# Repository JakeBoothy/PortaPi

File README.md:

# PortaPi
A portable Raspberry Pi Zero W2

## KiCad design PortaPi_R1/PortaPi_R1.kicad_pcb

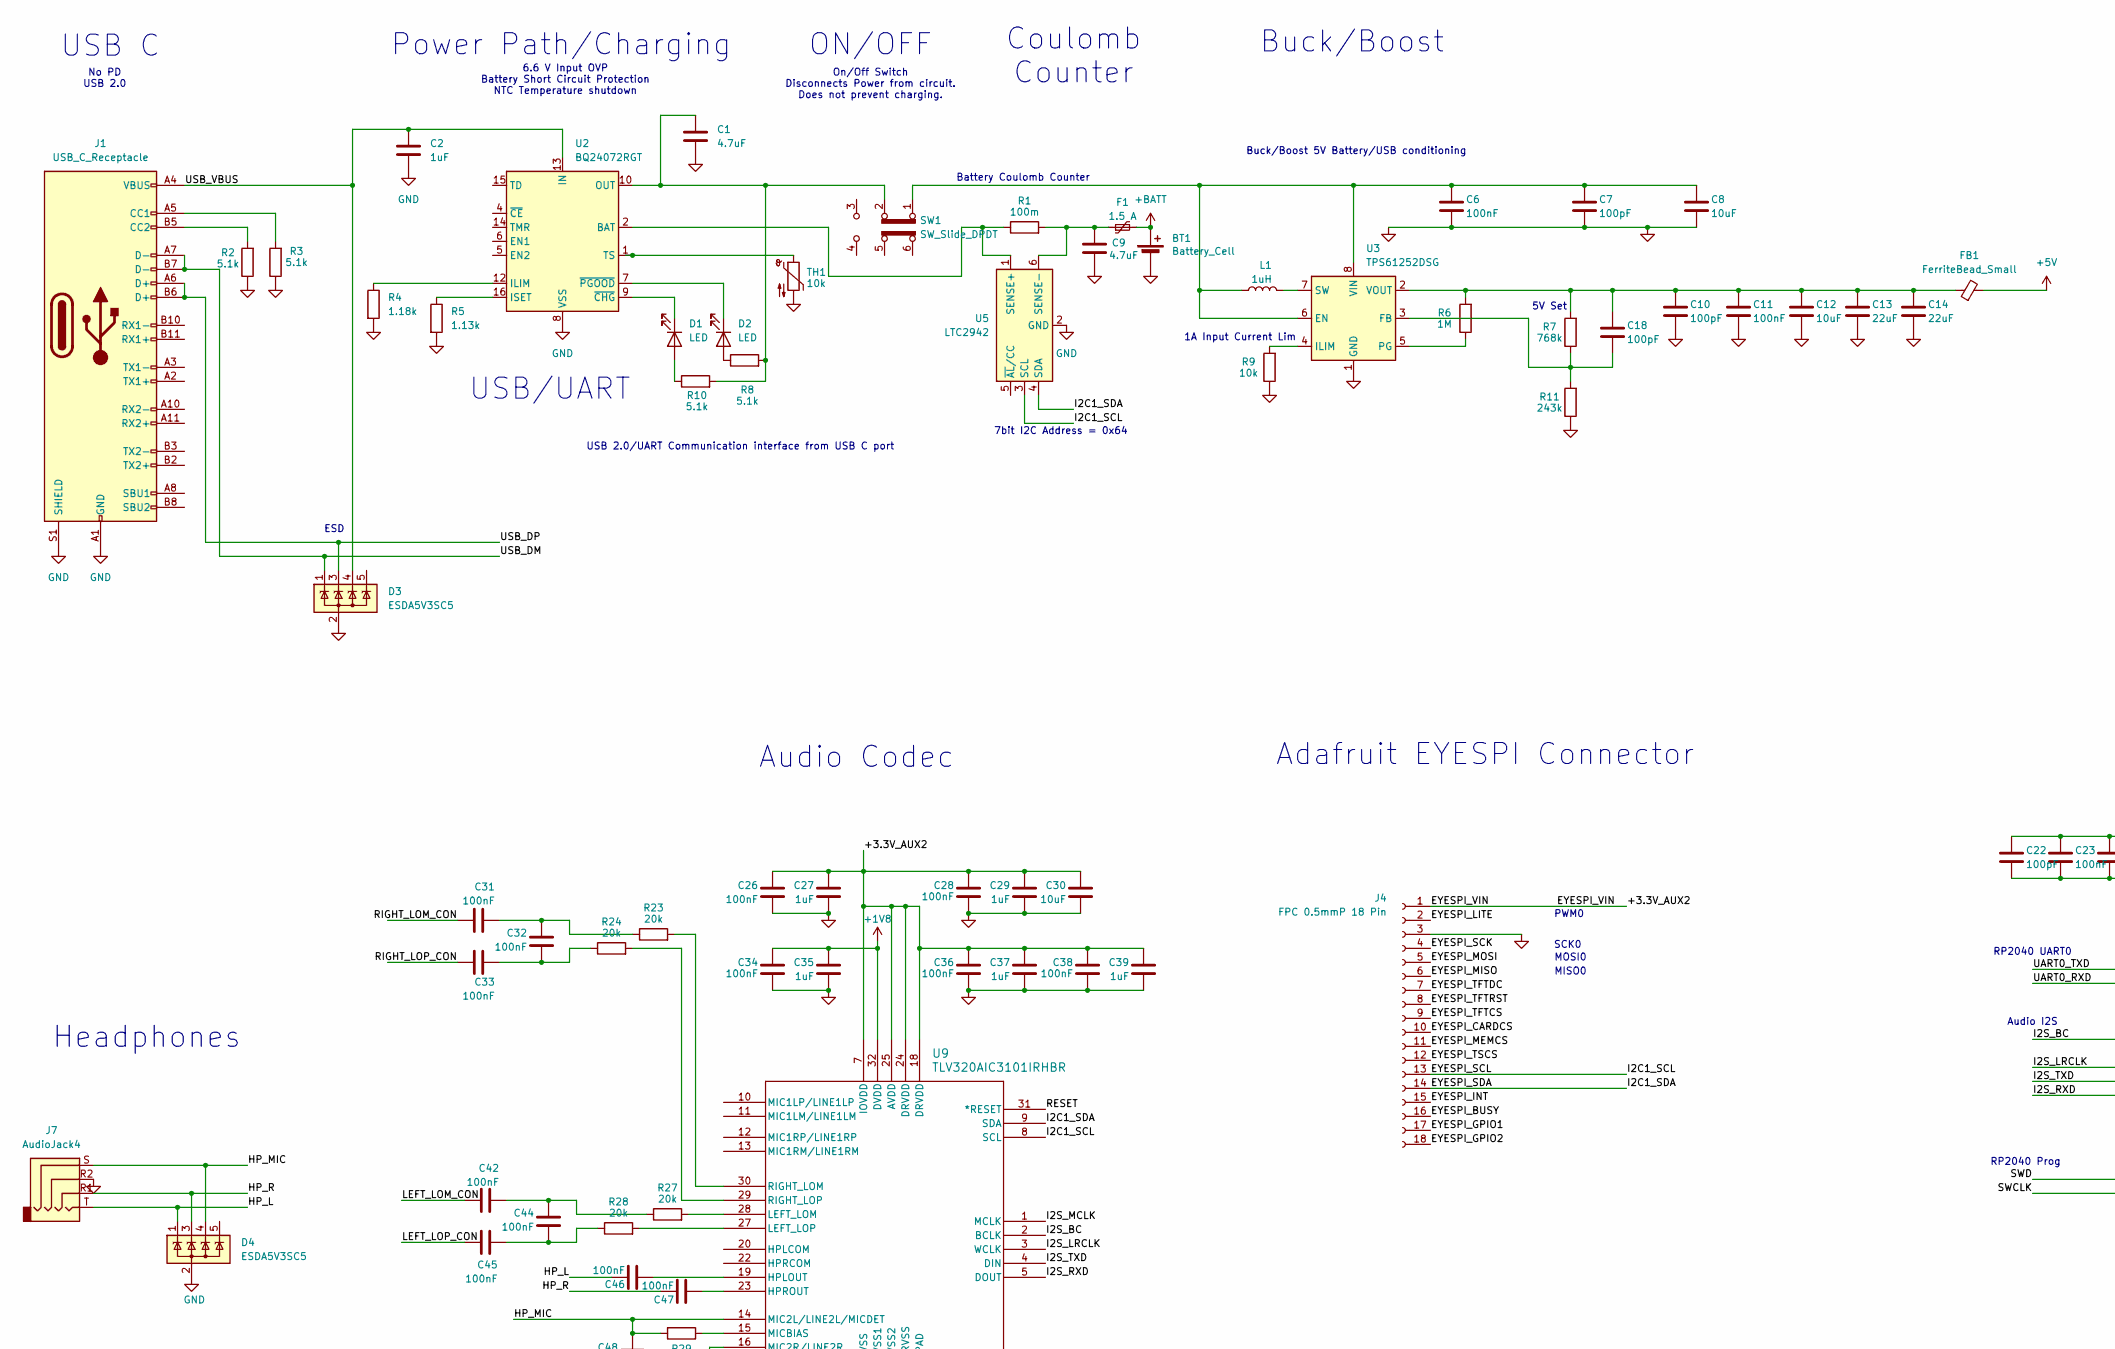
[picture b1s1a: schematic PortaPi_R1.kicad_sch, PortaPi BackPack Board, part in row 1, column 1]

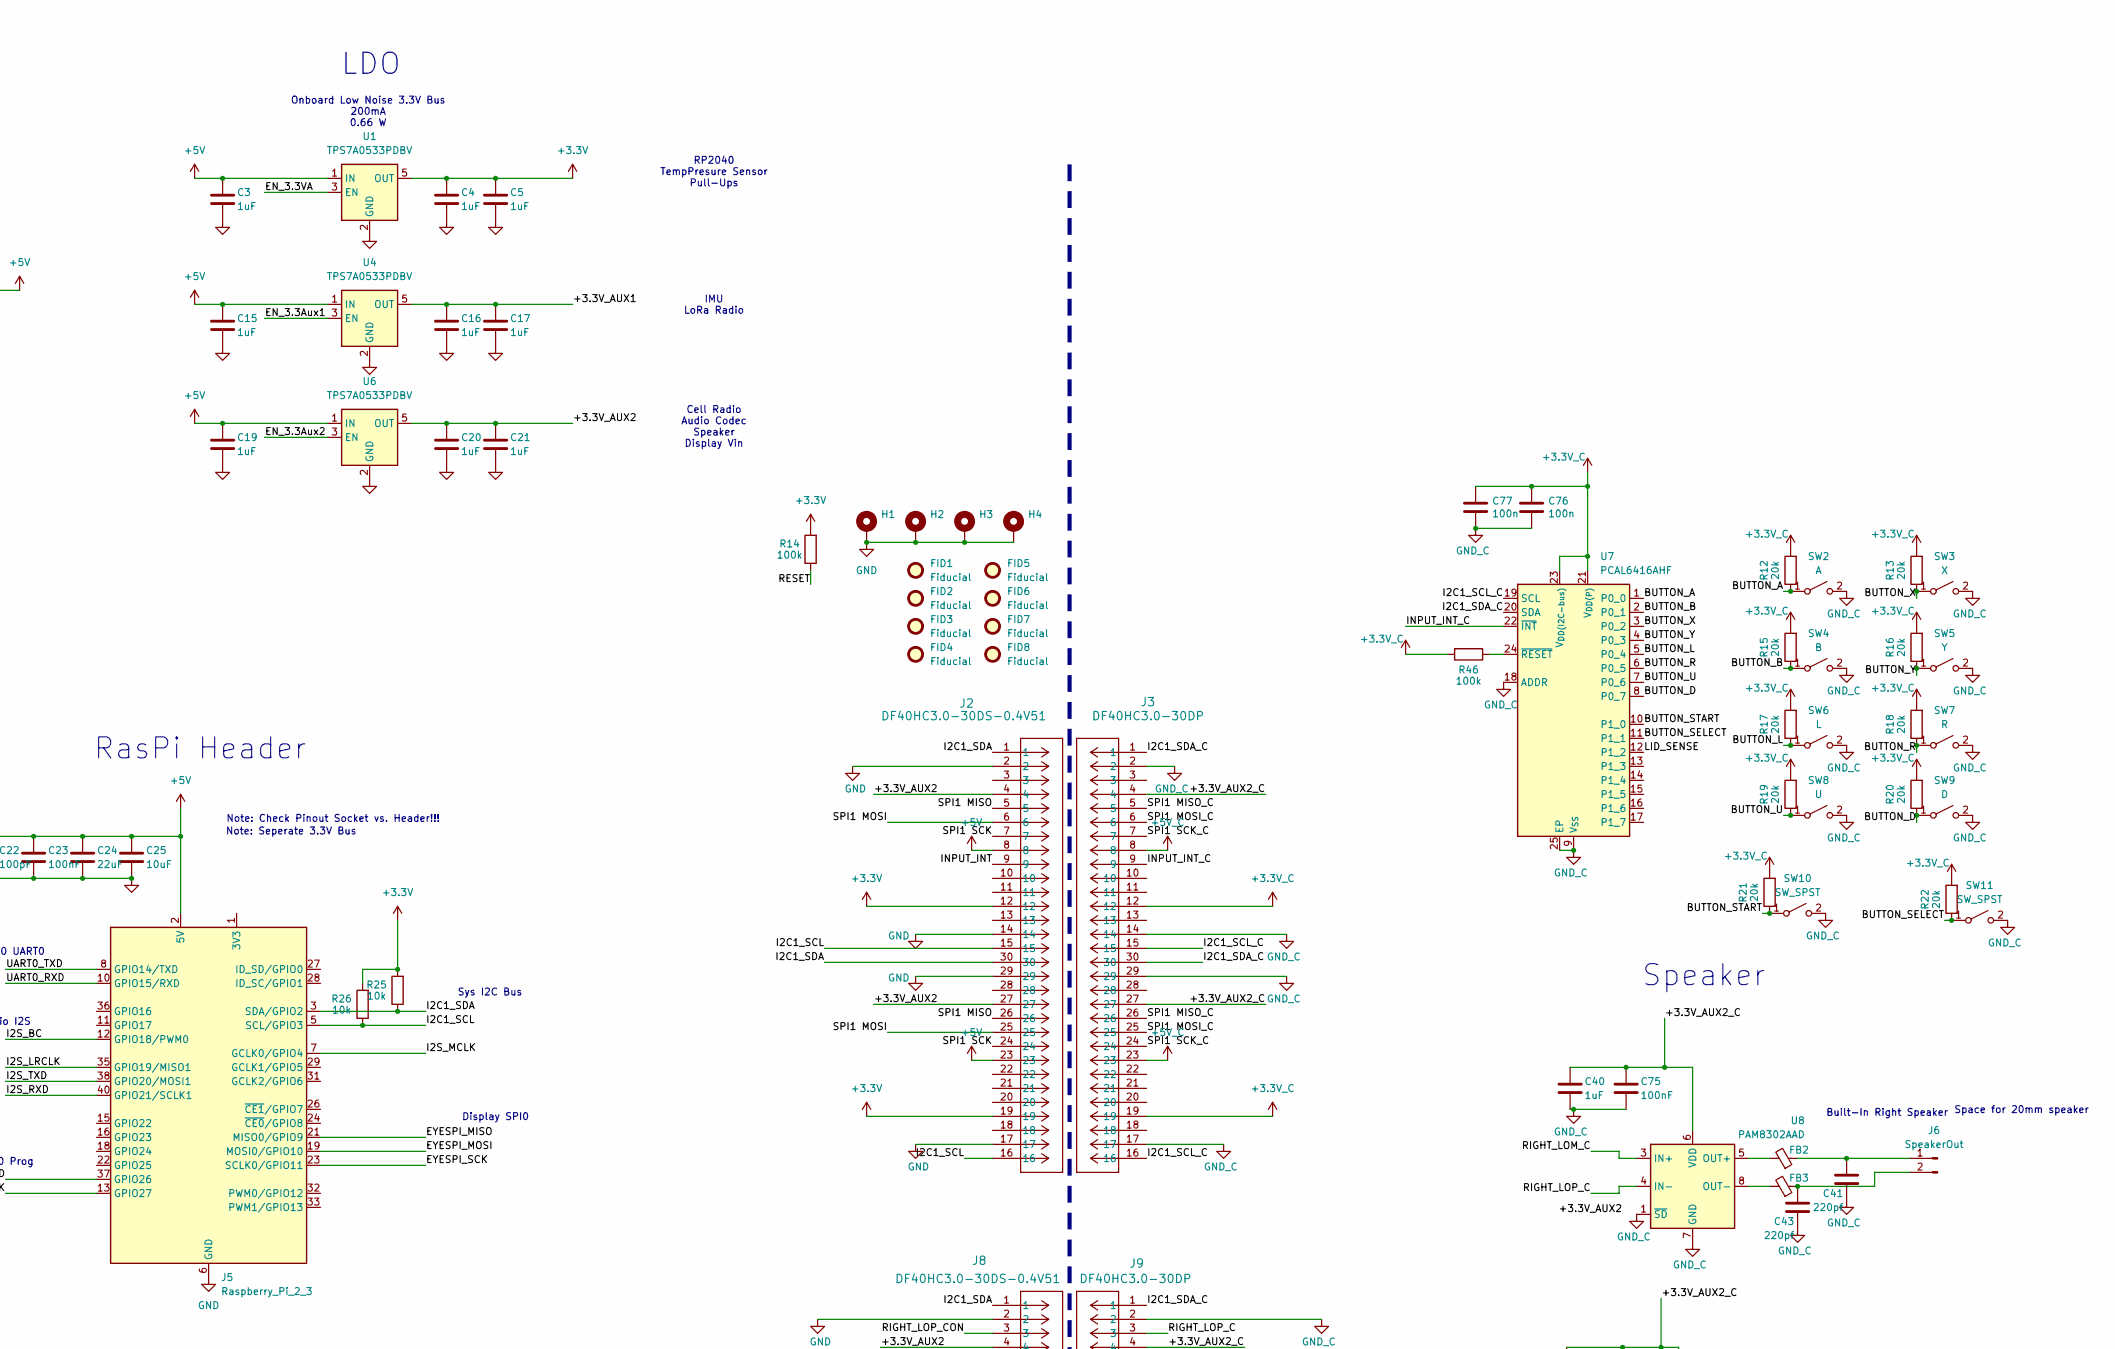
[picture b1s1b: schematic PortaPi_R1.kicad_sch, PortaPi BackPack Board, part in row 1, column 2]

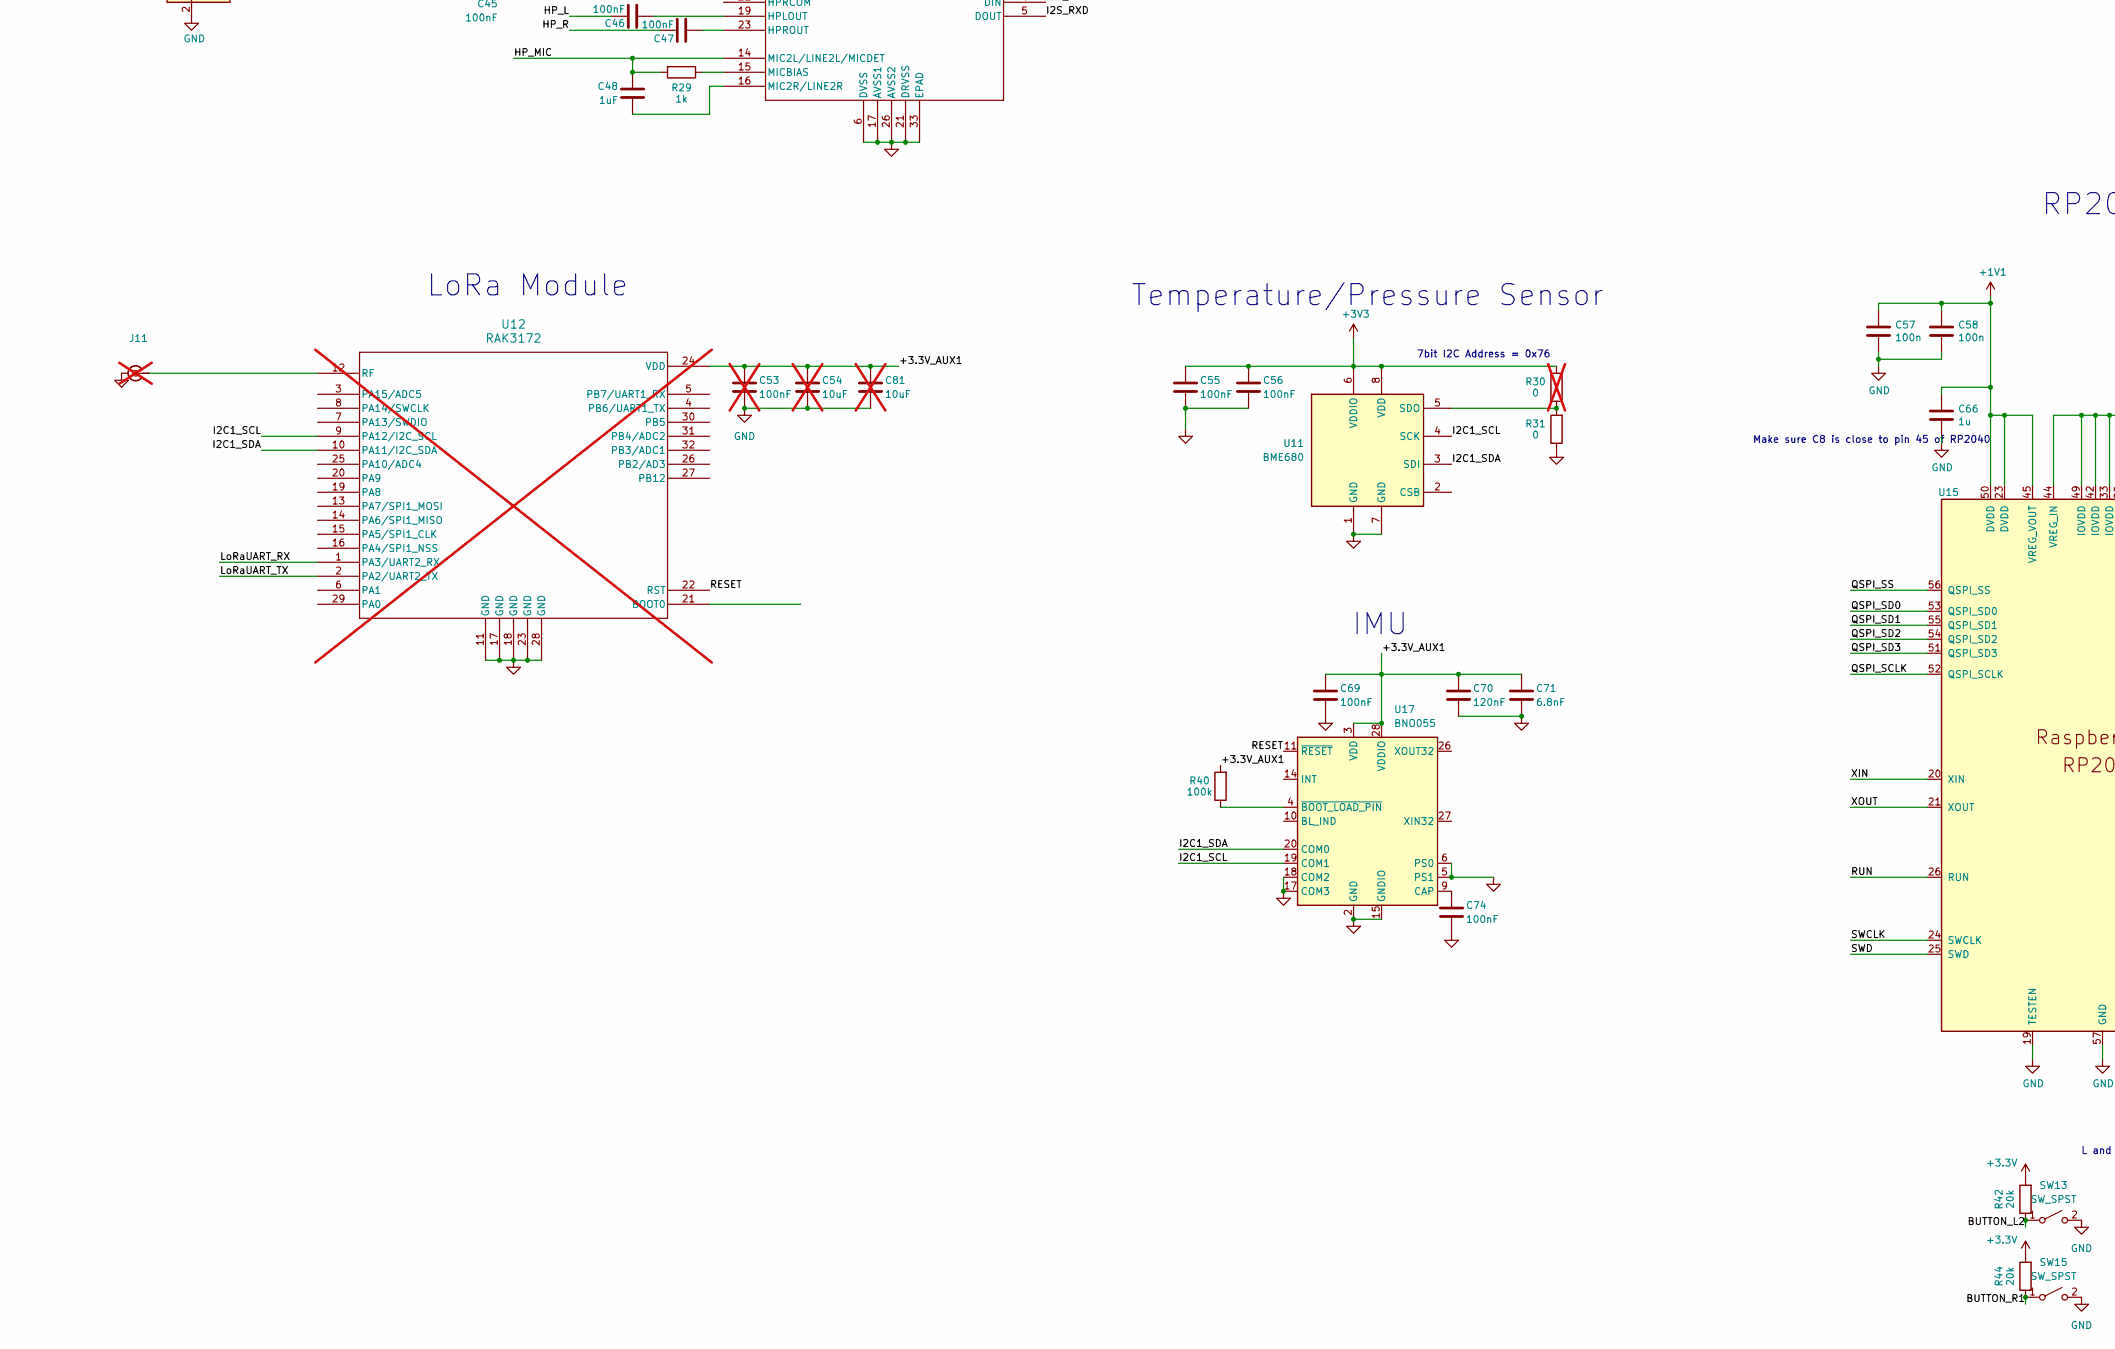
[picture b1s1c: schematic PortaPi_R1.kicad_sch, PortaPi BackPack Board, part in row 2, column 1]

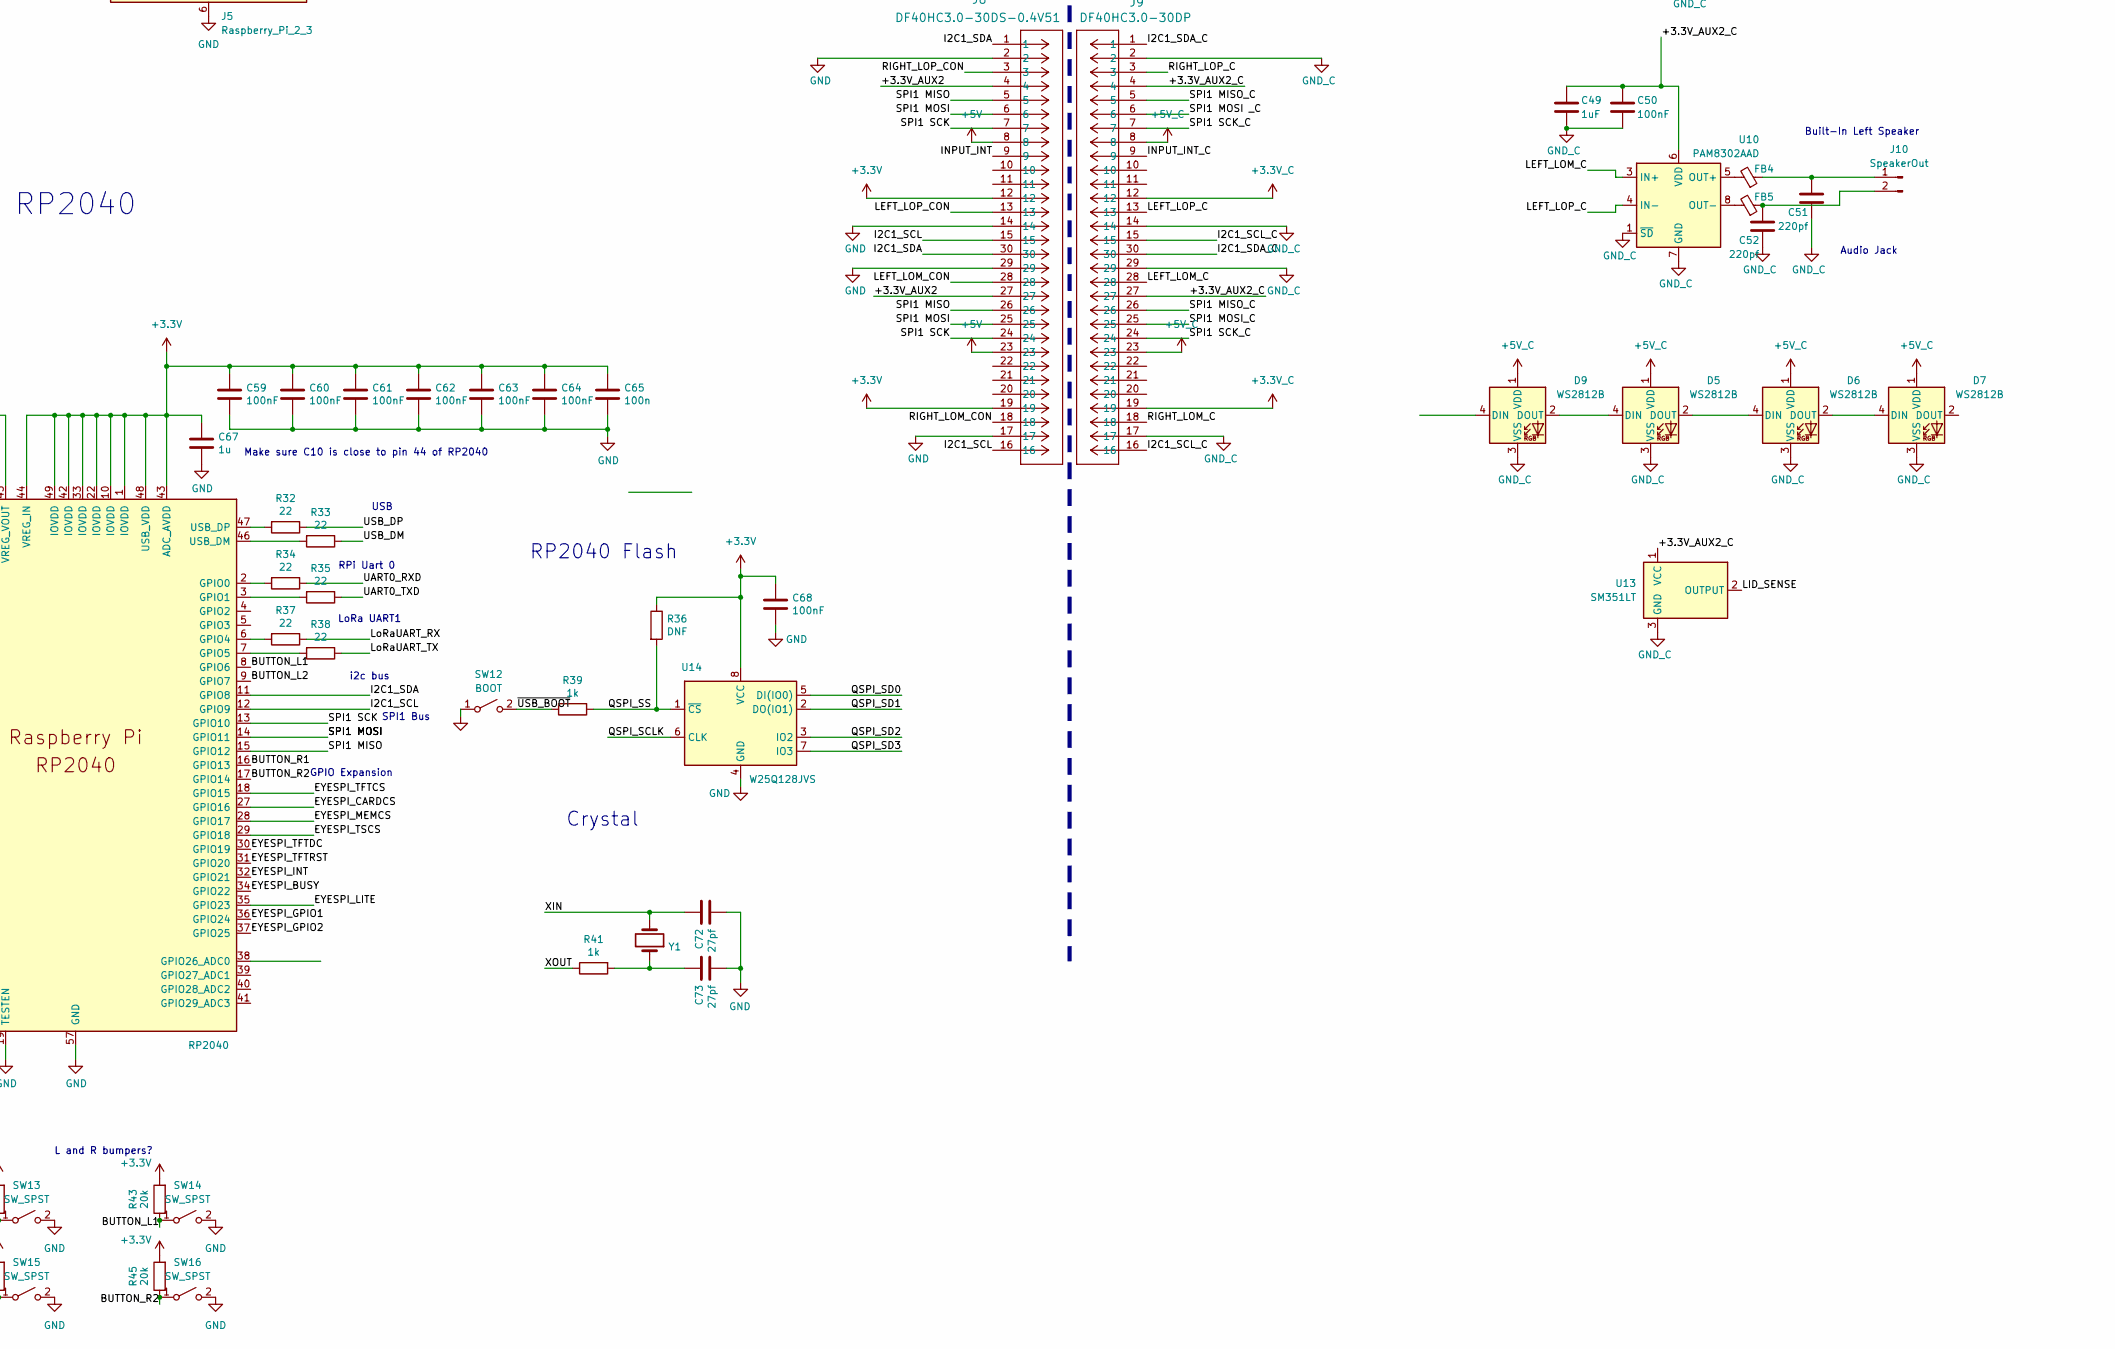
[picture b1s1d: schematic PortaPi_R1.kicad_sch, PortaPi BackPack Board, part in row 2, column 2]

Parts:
BT1: Battery_Cell; JST_PH_S2B-PH-SM4-TB_1x02-1MP_P2.00mm_Horizontal
C1, C9: 4.7uF; C_0805_2012Metric
C2, C3, C4, C5, C15, C16, C17, C19, C20, C21, C27, C29, C35, C37, C39, C40, C48, C49: 1uF; C_0603_1608Metric
C6, C11, C23, C26, C28, C31, C32, C33, C34, C36, C38, C42, C44, C45, C46, C47, C50, C55, C56, C68, C69, C74, C75: 100nF; C_0603_1608Metric
C7, C10, C18, C22: 100pF; C_0603_1608Metric
C8, C12, C25, C30: 10uF; C_0805_2012Metric
C13, C14, C24: 22uF; C_0805_2012Metric
C41, C43, C51, C52: 220pf; C_0603_1608Metric
C53: 100nF; C_0603_1608Metric; not fitted
C54, C81: 10uF; C_0805_2012Metric; not fitted
C57, C58, C65, C76, C77: 100n; C_0402_1005Metric
C59, C60, C61, C62, C63, C64: 100nF; C_0402_1005Metric
C66, C67: 1u; C_0402_1005Metric
C70: 120nF; C_0603_1608Metric
C71: 6.8nF; C_0603_1608Metric
C72, C73: 27pf; C_0402_1005Metric
D1, D2: LED; LED_0603_1608Metric
D3, D4: ESDA5V3SC5; SOT-23-5
D5, D6, D7, D9: WS2812B; LED_WS2812B_PLCC4_5.0x5.0mm_P3.2mm
F1: 1.5 A; R_0603_1608Metric
FB1: FerriteBead_Small; R_0603_1608Metric
FB2, FB3, FB4, FB5: FerriteBead_Small; L_0603_1608Metric
FID1, FID2, FID3, FID4, FID5, FID6, FID7, FID8: Fiducial; Fiducial_1.5mm_Mask3mm
H1, H2, H3, H4: MountingHole_Pad; MountingHole_2.5mm_Pad_Via
J1: USB_C_Receptacle; USB_C_Receptacle_GCT_USB4105-xx-A_16P_TopMnt_Horizontal
J2, J8: DF40HC3.0-30DS-0.4V51; CONN_30DS-0.4V51
J3, J9: DF40HC3.0-30DP; SOIC_0DP-0.4V51_HIR
J4: FPC 0.5mmP 18 Pin; TE_1-1734839-8_1x18-1MP_P0.5mm_Horizontal
J5: Raspberry_Pi_2_3; Raspberry_Pi_Zero_Socketed_THT_FaceDown_MountingHoles
J6, J10: SpeakerOut; SolderJumper-2_P1.3mm_Open_Pad1.0x1.5mm
J7: AudioJack4; Jack_3.5mm_PJ320D_Horizontal
J11: Conn_Coaxial_Small; U.FL_Molex_MCRF_73412-0110_Vertical; not fitted
L1: 1uH; L_Bourns-SRN4018
R1: 100m; R_0603_1608Metric
R2, R3, R8, R10: 5.1k; R_0603_1608Metric
R4: 1.18k; R_0603_1608Metric
R5: 1.13k; R_0603_1608Metric
R6: 1M; R_0603_1608Metric
R7: 768k; R_0603_1608Metric
R9, R25, R26: 10k; R_0603_1608Metric
R11: 243k; R_0603_1608Metric
R12, R13, R15, R16, R17, R18, R19, R20, R21, R22, R23, R24, R27, R28, R42, R43, R44, R45: 20k; R_0603_1608Metric
R14, R40, R46: 100k; R_0603_1608Metric
R29: 1k; C_0603_1608Metric
R30: 0; R_0603_1608Metric; not fitted
R31: 0; R_0603_1608Metric
R32, R33, R34, R35, R37, R38: 22; C_0402_1005Metric
R36: DNF; C_0402_1005Metric
R39, R41: 1k; C_0402_1005Metric
SW1: SW_Slide_DPDT; SW_SPDT_PCM12
SW2: A; SW_PUSH_6mm
SW3: X; SW_PUSH_6mm
SW4: B; SW_PUSH_6mm
SW5: Y; SW_PUSH_6mm
SW6: L; SW_PUSH_6mm
SW7: R; SW_PUSH_6mm
SW8: U; SW_PUSH_6mm
SW9: D; SW_PUSH_6mm
SW10, SW11: SW_SPST; SW_PUSH_6mm
SW12: BOOT; SW_SPST_B3U-1000P-B
SW13, SW14, SW15, SW16: SW_SPST; SW_Tactile_SPST_Angled_PTS645Vx31-2LFS
TH1: 10k; R_0603_1608Metric
U1, U4, U6: TPS7A0533PDBV; SOT-23-5
U2: BQ24072RGT; VQFN-16-1EP_3x3mm_P0.5mm_EP1.6x1.6mm
U3: TPS61252DSG; WSON-8-1EP_2x2mm_P0.5mm_EP0.9x1.6mm
U5: LTC2942; DFN-6-1EP_3x2mm_P0.5mm_EP1.65x1.35mm
U7: PCAL6416AHF; HVQFN-24-1EP_4x4mm_P0.5mm_EP2.1x2.1mm
U8, U10: PAM8302AAD; SOP-8_3.9x4.9mm_P1.27mm
U9: TLV320AIC3101IRHBR; RHB32_3P45X3P45
U11: BME680; Bosch_LGA-8_3x3mm_P0.8mm_ClockwisePinNumbering
U12: RAK3172; RAK3172_RAK; not fitted
U13: SM351LT; SOT-23
U14: W25Q128JVS; SOIC-8_5.23x5.23mm_P1.27mm
U15: RP2040; QFN-56-1EP_7x7mm_P0.4mm_EP3.2x3.2mm
U17: BNO055; LGA-28_5.2x3.8mm_P0.5mm
Y1: ABM3-12.000MHZ-D2Y-T; Crystal_SMD_5032-4Pin_5.0x3.2mm

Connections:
+1V1: C57.1, C58.1, C66.1, U15.23 (DVDD), U15.45 (VREG_VOUT), U15.50 (DVDD)
+1V8: C34.1, C35.1, U9.32 (DVDD)
+3.3V: C4.1, C5.1, C59.1, C60.1, C61.1, C62.1, C63.1, C64.1, C65.1, C67.1, C68.1, J2.12, J2.19, J8.12, J8.19, R14.2, R25.2, R26.2, R36.1, R42.2, R43.2, R44.2, R45.2, U1.5 (OUT), U14.8 (VCC), U15.1 (IOVDD), U15.10 (IOVDD), U15.22 (IOVDD), U15.33 (IOVDD), U15.42 (IOVDD), U15.43 (ADC_AVDD), U15.44 (VREG_IN), U15.48 (USB_VDD), U15.49 (IOVDD)
+3.3V_C: C76.1, C77.1, J3.12, J3.19, J9.12, J9.19, R12.2, R13.2, R15.2, R16.2, R17.2, R18.2, R19.2, R20.2, R21.2, R22.2, R46.2, U7.21 (V_{DD(P)}), U7.23 (V_{DD(I2C-bus)})
+3V3: C55.1, C56.1, R30.2, U11.6 (VDDIO), U11.8 (VDD)
+5V: C3.1, C15.1, C19.1, C22.1, C23.1, C24.1, C25.1, FB1.2, J2.8, J2.23, J5.2 (5V), J5.4 (5V), J8.8, J8.23, U1.1 (IN), U4.1 (IN), U6.1 (IN)
+5V_C: D5.1 (VDD), D6.1 (VDD), D7.1 (VDD), D9.1 (VDD), J3.8, J3.23, J9.8, J9.23
+BATT: BT1.1 (+), F1.2
/+3.3V_AUX1: C16.1, C17.1, C53.1, C54.1, C69.1, C70.1, C71.1, C81.1, R40.2, U4.5 (OUT), U12.24 (VDD), U17.3 (VDD), U17.28 (VDDIO)
/+3.3V_AUX2: C20.1, C21.1, C26.1, C27.1, C28.1, C29.1, C30.1, C36.1, C37.1, C38.1, C39.1, J2.4, J2.27, J4.1, J8.4, J8.27, U6.5 (OUT), U9.7 (IOVDD), U9.18 (DRVDD), U9.24 (DRVDD), U9.25 (AVDD)
/+3.3V_AUX2_C: C40.1, C49.1, C50.1, C75.1, J3.4, J3.27, J9.4, J9.27, U8.6 (VDD), U10.6 (VDD), U13.1 (VCC)
/BUTTON_A: R12.1, SW2.1 (A), U7.1 (P0_0)
/BUTTON_B: R15.1, SW4.1 (A), U7.2 (P0_1)
/BUTTON_D: R20.1, SW9.1 (A), U7.8 (P0_7)
/BUTTON_L: R17.1, SW6.1 (A), U7.5 (P0_4)
/BUTTON_L1: R43.1, SW14.1 (A), U15.8 (GPIO6)
/BUTTON_L2: R42.1, SW13.1 (A), U15.9 (GPIO7)
/BUTTON_R: R18.1, SW7.1 (A), U7.6 (P0_5)
/BUTTON_R1: R44.1, SW15.1 (A), U15.16 (GPIO13)
/BUTTON_R2: R45.1, SW16.1 (A), U15.17 (GPIO14)
/BUTTON_SELECT: R22.1, SW11.1 (A), U7.11 (P1_1)
/BUTTON_START: R21.1, SW10.1 (A), U7.10 (P1_0)
/BUTTON_U: R19.1, SW8.1 (A), U7.7 (P0_6)
/BUTTON_X: R13.1, SW3.1 (A), U7.3 (P0_2)
/BUTTON_Y: R16.1, SW5.1 (A), U7.4 (P0_3)
/EN_3.3Aux1: U4.3 (EN)
/EN_3.3Aux2: U6.3 (EN)
/EN_3.3VA: U1.3 (EN)
/EYESPI_BUSY: J4.16, U15.34 (GPIO22)
/EYESPI_CARDCS: J4.10, U15.27 (GPIO16)
/EYESPI_GPIO1: J4.17, U15.36 (GPIO24)
/EYESPI_GPIO2: J4.18, U15.37 (GPIO25)
/EYESPI_INT: J4.15, U15.32 (GPIO21)
/EYESPI_LITE: J4.2, U15.35 (GPIO23)
/EYESPI_MEMCS: J4.11, U15.28 (GPIO17)
/EYESPI_MISO: J4.6, J5.21 (MISO0/GPIO9)
/EYESPI_MOSI: J4.5, J5.19 (MOSI0/GPIO10)
/EYESPI_SCK: J4.4, J5.23 (SCLK0/GPIO11)
/EYESPI_SCL: J2.15, J2.16, J4.13, J5.5 (SCL/GPIO3), J8.15, J8.16, R26.1, U5.3 (SCL), U9.8 (SCL), U11.4 (SCK), U12.9 (PA12/I2C_SCL), U15.12 (GPIO9), U17.19 (COM1)
/EYESPI_SDA: J2.1, J2.30, J4.14, J5.3 (SDA/GPIO2), J8.1, J8.30, R25.1, U5.4 (SDA), U9.9 (SDA), U11.3 (SDI), U12.10 (PA11/I2C_SDA), U15.11 (GPIO8), U17.20 (COM0)
/EYESPI_TFTCS: J4.9, U15.18 (GPIO15)
/EYESPI_TFTDC: J4.7, U15.30 (GPIO19)
/EYESPI_TFTRST: J4.8, U15.31 (GPIO20)
/EYESPI_TSCS: J4.12, U15.29 (GPIO18)
/HP_L: C46.1, D4.1 (K), J7.T
/HP_MIC: C48.1, D4.4 (K), J7.S, R29.2, U9.14 (MIC2L/LINE2L/MICDET)
/HP_R: C47.1, D4.3 (K), J7.R1
/I2C1_SCL_C: J3.15, J3.16, J9.15, J9.16, U7.19 (SCL)
/I2C1_SDA_C: J3.1, J3.30, J9.1, J9.30, U7.20 (SDA)
/I2S_BC: J5.12 (GPIO18/PWM0), U9.2 (BCLK)
/I2S_LRCLK: J5.35 (GPIO19/MISO1), U9.3 (WCLK)
/I2S_MCLK: J5.7 (GCLK0/GPIO4), U9.1 (MCLK)
/I2S_RXD: J5.40 (GPIO21/SCLK1), U9.5 (DOUT)
/I2S_TXD: J5.38 (GPIO20/MOSI1), U9.4 (DIN)
/INPUT_INT: J2.9, J8.9
/INPUT_INT_C: J3.9, J9.9, U7.22 (~INT)
/LEFT_LOM_C: J9.28, U10.3 (IN+)
/LEFT_LOM_CON: C42.1, J8.28
/LEFT_LOP_C: J9.13, U10.4 (IN-)
/LEFT_LOP_CON: C45.1, J8.13
/LID_SENSE: U7.12 (P1_2), U13.2 (OUTPUT)
/LoRaUART_RX: R37.1, U12.1 (PA3/UART2_RX)
/LoRaUART_TX: R38.1, U12.2 (PA2/UART2_TX)
/QSPI_SCLK: U14.6 (CLK), U15.52 (QSPI_SCLK)
/QSPI_SD0: U14.5 (DI(IO0)), U15.53 (QSPI_SD0)
/QSPI_SD1: U14.2 (DO(IO1)), U15.55 (QSPI_SD1)
/QSPI_SD2: U14.3 (IO2), U15.54 (QSPI_SD2)
/QSPI_SD3: U14.7 (IO3), U15.51 (QSPI_SD3)
/QSPI_SS: R36.2, R39.1, U14.1 (~CS), U15.56 (QSPI_SS)
/RESET: R14.1, U9.31 (*RESET), U12.22 (RST), U17.11 (~RESET)
/RIGHT_LOM_C: J9.18, U8.3 (IN+)
/RIGHT_LOM_CON: C31.1, J8.18
/RIGHT_LOP_C: J9.3, U8.4 (IN-)
/RIGHT_LOP_CON: C33.1, J8.3
/RUN: U15.26 (RUN)
/SPI1 MISO: J2.5, J2.26, J8.5, J8.26, U15.15 (GPIO12)
/SPI1 MISO_C: J3.5, J3.26, J9.5, J9.26
/SPI1 MOSI: J2.6, J2.25, J8.6, J8.25, U15.14 (GPIO11)
/SPI1 MOSI _C: J9.6
/SPI1 MOSI_C: J3.6, J3.25, J9.25
/SPI1 SCK: J2.7, J2.24, J8.7, J8.24, U15.13 (GPIO10)
/SPI1 SCK_C: J3.7, J3.24, J9.7, J9.24
/SWCLK: J5.13 (GPIO27), U15.24 (SWCLK)
/SWD: J5.37 (GPIO26), U15.25 (SWD)
/UART0_RXD: J5.10 (GPIO15/RXD), R34.1
/UART0_TXD: J5.8 (GPIO14/TXD), R35.1
/USB_DM: D3.1 (K), J1.A7 (D-), J1.B7 (D-), R33.1
/USB_DP: D3.3 (K), J1.A6 (D+), J1.B6 (D+), R32.1
/USB_VBUS: C2.1, D3.4 (K), J1.A4 (VBUS), J1.A9 (VBUS), J1.B4 (VBUS), J1.B9 (VBUS), U2.13 (IN)
/XIN: C72.1, U15.20 (XIN), Y1.2
/XOUT: R41.1, U15.21 (XOUT)
/~USB_BOOT: R39.2, SW12.2 (B)
GND: BT1.2 (-), C1.2, C2.2, C3.2, C4.2, C5.2, C6.2, C7.2, C8.2, C9.2, C10.2, C11.2, C12.2, C13.2, C14.2, C15.2, C16.2, C17.2, C19.2, C20.2, C21.2, C22.2, C23.2, C24.2, C25.2, C26.2, C27.2, C28.2, C29.2, C30.2, C34.2, C35.2, C36.2, C37.2, C38.2, C39.2, C53.2, C54.2, C55.2, C56.2, C57.2, C58.2, C59.2, C60.2, C61.2, C62.2, C63.2, C64.2, C65.2, C66.2, C67.2, C68.2, C69.2, C70.2, C71.2, C72.2, C73.2, C74.2, C81.2, D3.2 (A), D4.2 (A), H1.1, H2.1, H3.1, H4.1, J1.A1 (GND), J1.A12 (GND), J1.B1 (GND), J1.B12 (GND), J1.S1 (SHIELD), J2.2, J2.14, J2.17, J2.29, J4.3, J5.6 (GND), J5.9 (GND), J5.14 (GND), J5.20 (GND), J5.25 (GND), J5.30 (GND), J5.34 (GND), J5.39 (GND), J7.R2, J8.2, J8.14, J8.17, J8.29, J11.2 (Ext), R2.1, R3.1, R4.2, R5.2, R9.1, R11.1, R31.1, SW12.1 (A), SW13.2 (B), SW14.2 (B), SW15.2 (B), SW16.2 (B), TH1.2, U1.2 (GND), U2.8 (VSS), U2.17 (VSS), U3.1 (GND), U3.9 (GND), U4.2 (GND), U5.2 (GND), U6.2 (GND), U9.6 (DVSS), U9.17 (AVSS1), U9.21 (DRVSS), U9.26 (AVSS2), U9.33 (EPAD), U11.1 (GND), U11.7 (GND), U12.11 (GND), U12.17 (GND), U12.18 (GND), U12.23 (GND), U12.28 (GND), U14.4 (GND), U15.19 (TESTEN), U15.57 (GND), U17.2 (GND), U17.5 (PS1), U17.6 (PS0), U17.15 (GNDIO), U17.16 (GNDIO), U17.17 (COM3), U17.18 (COM2), U17.25 (GNDIO)
GND_C: C40.2, C41.1, C43.1, C49.2, C50.2, C51.1, C52.1, C75.2, C76.2, C77.2, D5.3 (VSS), D6.3 (VSS), D7.3 (VSS), D9.3 (VSS), J3.2, J3.14, J3.17, J3.29, J9.2, J9.14, J9.17, J9.29, SW2.2 (B), SW3.2 (B), SW4.2 (B), SW5.2 (B), SW6.2 (B), SW7.2 (B), SW8.2 (B), SW9.2 (B), SW10.2 (B), SW11.2 (B), U7.9 (V_{SS}), U7.18 (ADDR), U7.25 (EP), U8.1 (~SD), U8.7 (GND), U10.1 (~SD), U10.7 (GND), U13.3 (GND)
unnamed: C1.1, R8.2, R10.2, SW1.2 (B), U2.10 (OUT), U2.11 (OUT)
unnamed: C31.2, C32.1, R23.1
unnamed: C32.2, C33.2, R24.1
unnamed: C42.2, C44.1, R27.1
unnamed: C44.2, C45.2, R28.1
unnamed: C73.1, R41.2, Y1.1
unnamed: D1.2 (A), R10.1
unnamed: D1.1 (K), U2.9 (~CHG)
unnamed: D2.2 (A), R8.1
unnamed: D2.1 (K), U2.7 (~PGOOD)
unnamed: D5.4 (DIN), D9.2 (DOUT)
unnamed: D5.2 (DOUT), D6.4 (DIN)
unnamed: D6.2 (DOUT), D7.4 (DIN)
unnamed: J1.A5 (CC1), R3.2
unnamed: J1.B5 (CC2), R2.2
unnamed: J5.1 (3V3), J5.17 (3V3)
unnamed: C41.2, FB2.1, J6.1
unnamed: C43.2, FB3.1, J6.2
unnamed: C51.2, FB4.1, J10.1
unnamed: C52.2, FB5.1, J10.2
unnamed: J11.1 (In), U12.12 (RF)
unnamed: R4.1, U2.12 (ILIM)
unnamed: R5.1, U2.16 (ISET)
unnamed: TH1.1, U2.1 (TS)
unnamed: C6.1, C7.1, C8.1, L1.1, SW1.1 (A), U3.6 (EN), U3.8 (VIN)
unnamed: C18.2, R7.1, R11.2, U3.3 (FB)
unnamed: R9.2, U3.4 (ILIM)
unnamed: R6.1, U3.5 (PG)
unnamed: L1.2, U3.7 (SW)
unnamed: C10.1, C11.1, C12.1, C13.1, C14.1, C18.1, FB1.1, R6.2, R7.2, U3.2 (VOUT)
unnamed: R1.1, U2.2 (BAT), U2.3 (BAT), U5.1 (SENSE+)
unnamed: C9.1, F1.1, R1.2, U5.6 (SENSE-)
unnamed: R46.1, U7.24 (~RESET)
unnamed: FB2.2, U8.5 (OUT+)
unnamed: FB3.2, U8.8 (OUT-)
unnamed: C46.2, U9.19 (HPLOUT)
unnamed: C47.2, U9.23 (HPROUT)
unnamed: R27.2, U9.28 (LEFT_LOM)
unnamed: R28.2, U9.27 (LEFT_LOP)
unnamed: C48.2, U9.16 (MIC2R/LINE2R)
unnamed: R29.1, U9.15 (MICBIAS)
unnamed: R23.2, U9.30 (RIGHT_LOM)
unnamed: R24.2, U9.29 (RIGHT_LOP)
unnamed: FB4.2, U10.5 (OUT+)
unnamed: FB5.2, U10.8 (OUT-)
unnamed: R30.1, R31.2, U11.5 (SDO)
unnamed: R34.2, U15.2 (GPIO0)
unnamed: R35.2, U15.3 (GPIO1)
unnamed: R37.2, U15.6 (GPIO4)
unnamed: R38.2, U15.7 (GPIO5)
unnamed: R33.2, U15.46 (USB_DM)
unnamed: R32.2, U15.47 (USB_DP)
unnamed: C74.1, U17.9 (CAP)
unnamed: R40.1, U17.4 (~BOOT_LOAD_PIN)

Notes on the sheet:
Display SPI0
Coulomb Counter
Adafruit EYESPI Connector
LoRa Module
Onboard Low Noise 3.3V Bus 200mA 0.66 W
USB C
7bit I2C Address = 0x64
Built-In Right Speaker
MISO0
USB/UART
RPi Uart 0
RasPi Header
Space for 20mm speaker
RP2040 TempPresure Sensor Pull-Ups
Make sure C8 is close to pin 45 of RP2040
RP2040 Prog
On/Off Switch Disconnects Power from circuit. Does not prevent charging.
Built-In Left Speaker
No PD USB 2.0
SCK0
Cell Radio Audio Codec Speaker Display Vin
Speaker
Power Path/Charging
GPIO Expansion
Make sure C10 is close to pin 44 of RP2040
Buck/Boost
Crystal
MOSI0
Buck/Boost 5V Battery/USB conditioning
Note: Check Pinout Socket vs. Header!!!
USB 2.0/UART Communication interface from USB C port
5V Set
IMU
Audio I2S
ESD
Audio Codec
Sys I2C Bus
1A Input Current Lim
LoRa UART1
IMU LoRa Radio

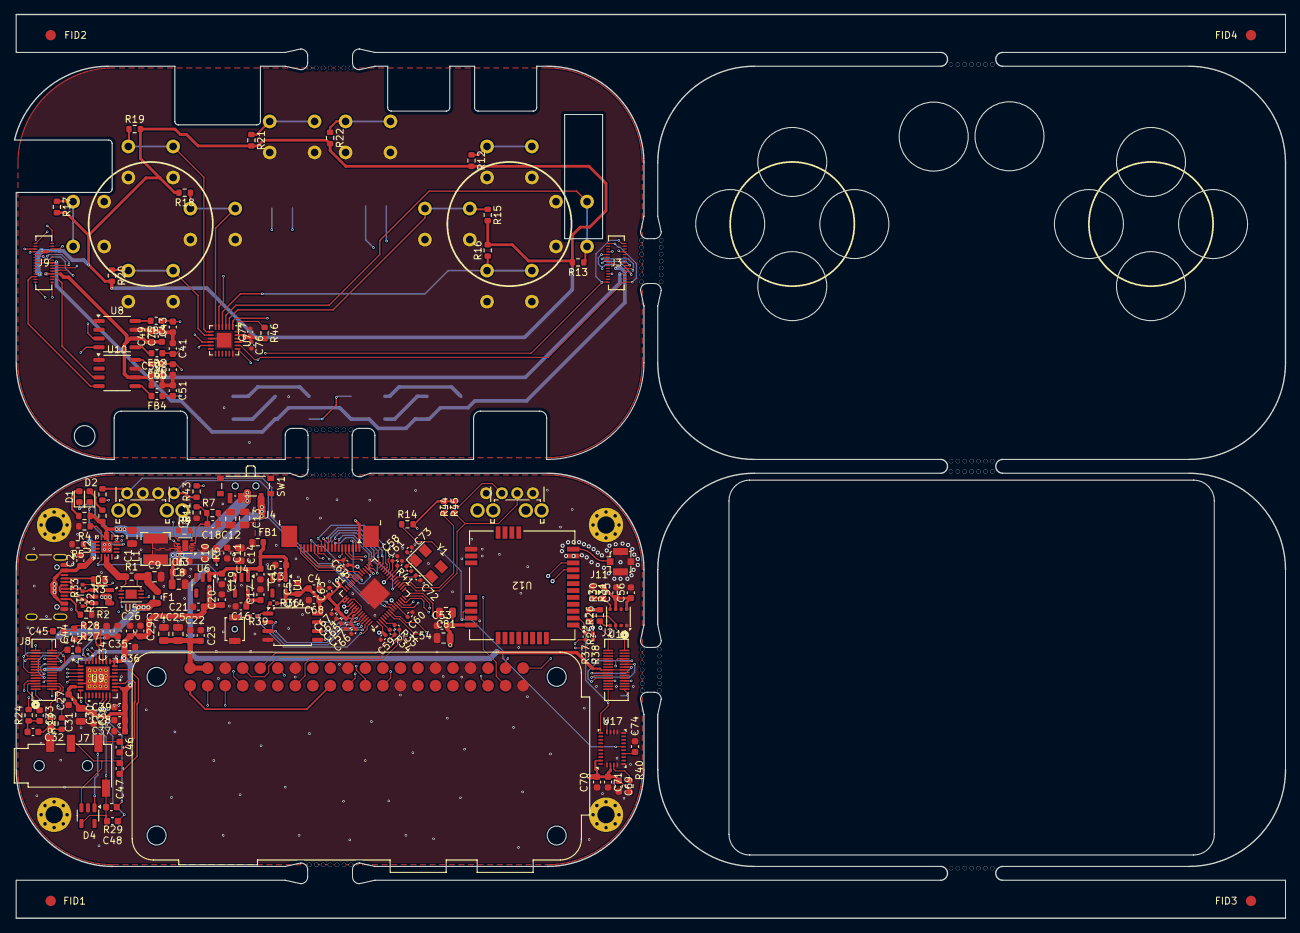
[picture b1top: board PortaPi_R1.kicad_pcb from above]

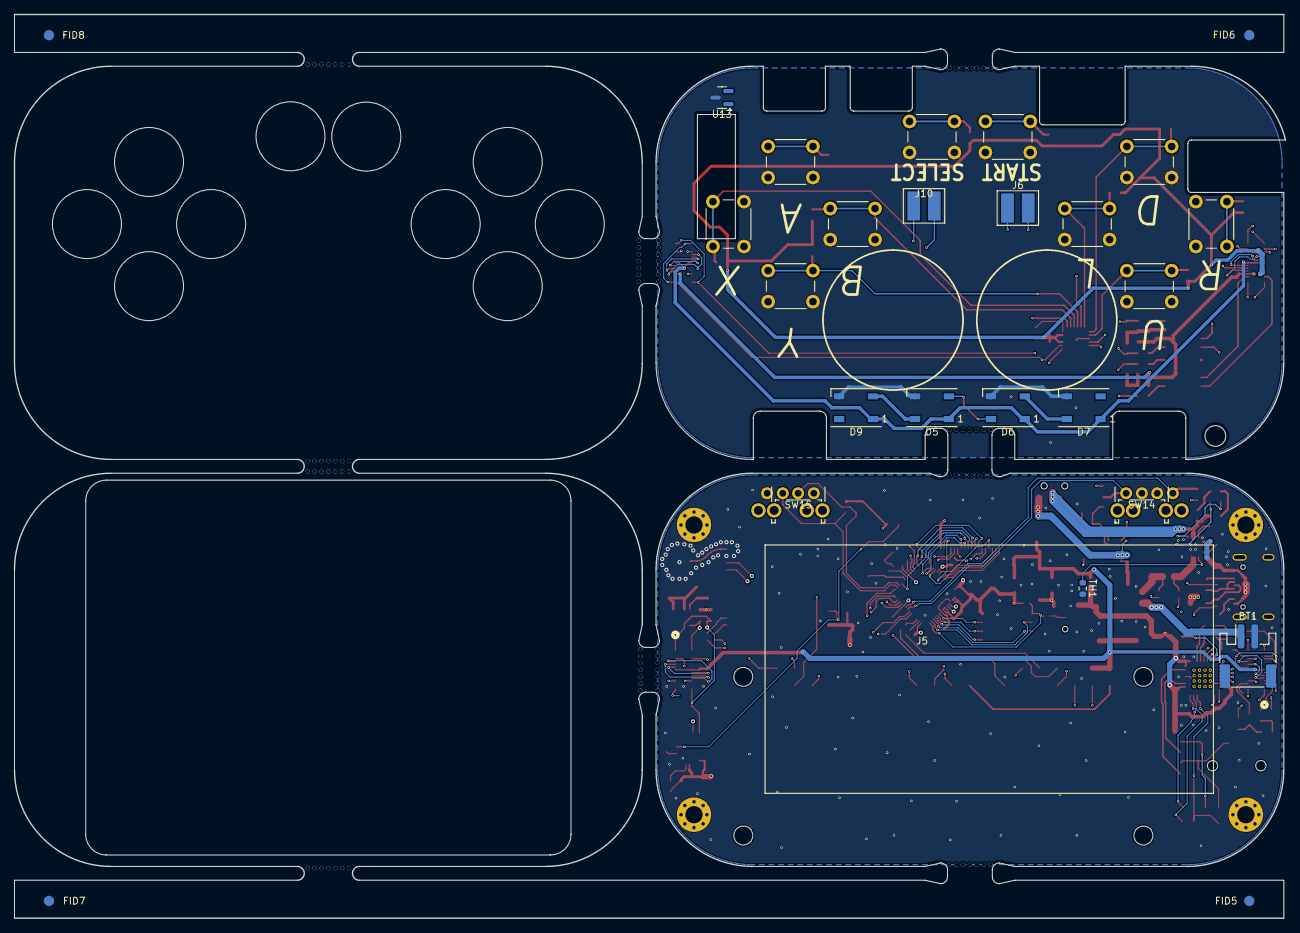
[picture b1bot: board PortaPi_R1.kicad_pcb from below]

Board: 4 copper layers, 184.2 x 131.0 mm, 197 parts (26 on the bottom side), 143 nets.

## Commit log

2024-06-09 init commit
2024-06-16 basic part picking
2024-06-17 additions
2024-07-01 designed power path/regulator ect...
2024-07-01 created altoids tin and boundary as footprints
2024-07-04 lots of new work and features
2024-07-06 starting layout
2024-07-07 more routing
2024-07-12 placing and routing
2024-07-12 routing work
2024-07-14 lots more routing work
2024-07-14 placing work
2024-07-15 routing and placinggit add .!
2024-07-15 routing...
2024-07-19 routing
2024-07-21 nearly done routing....
2024-07-30 misc work
